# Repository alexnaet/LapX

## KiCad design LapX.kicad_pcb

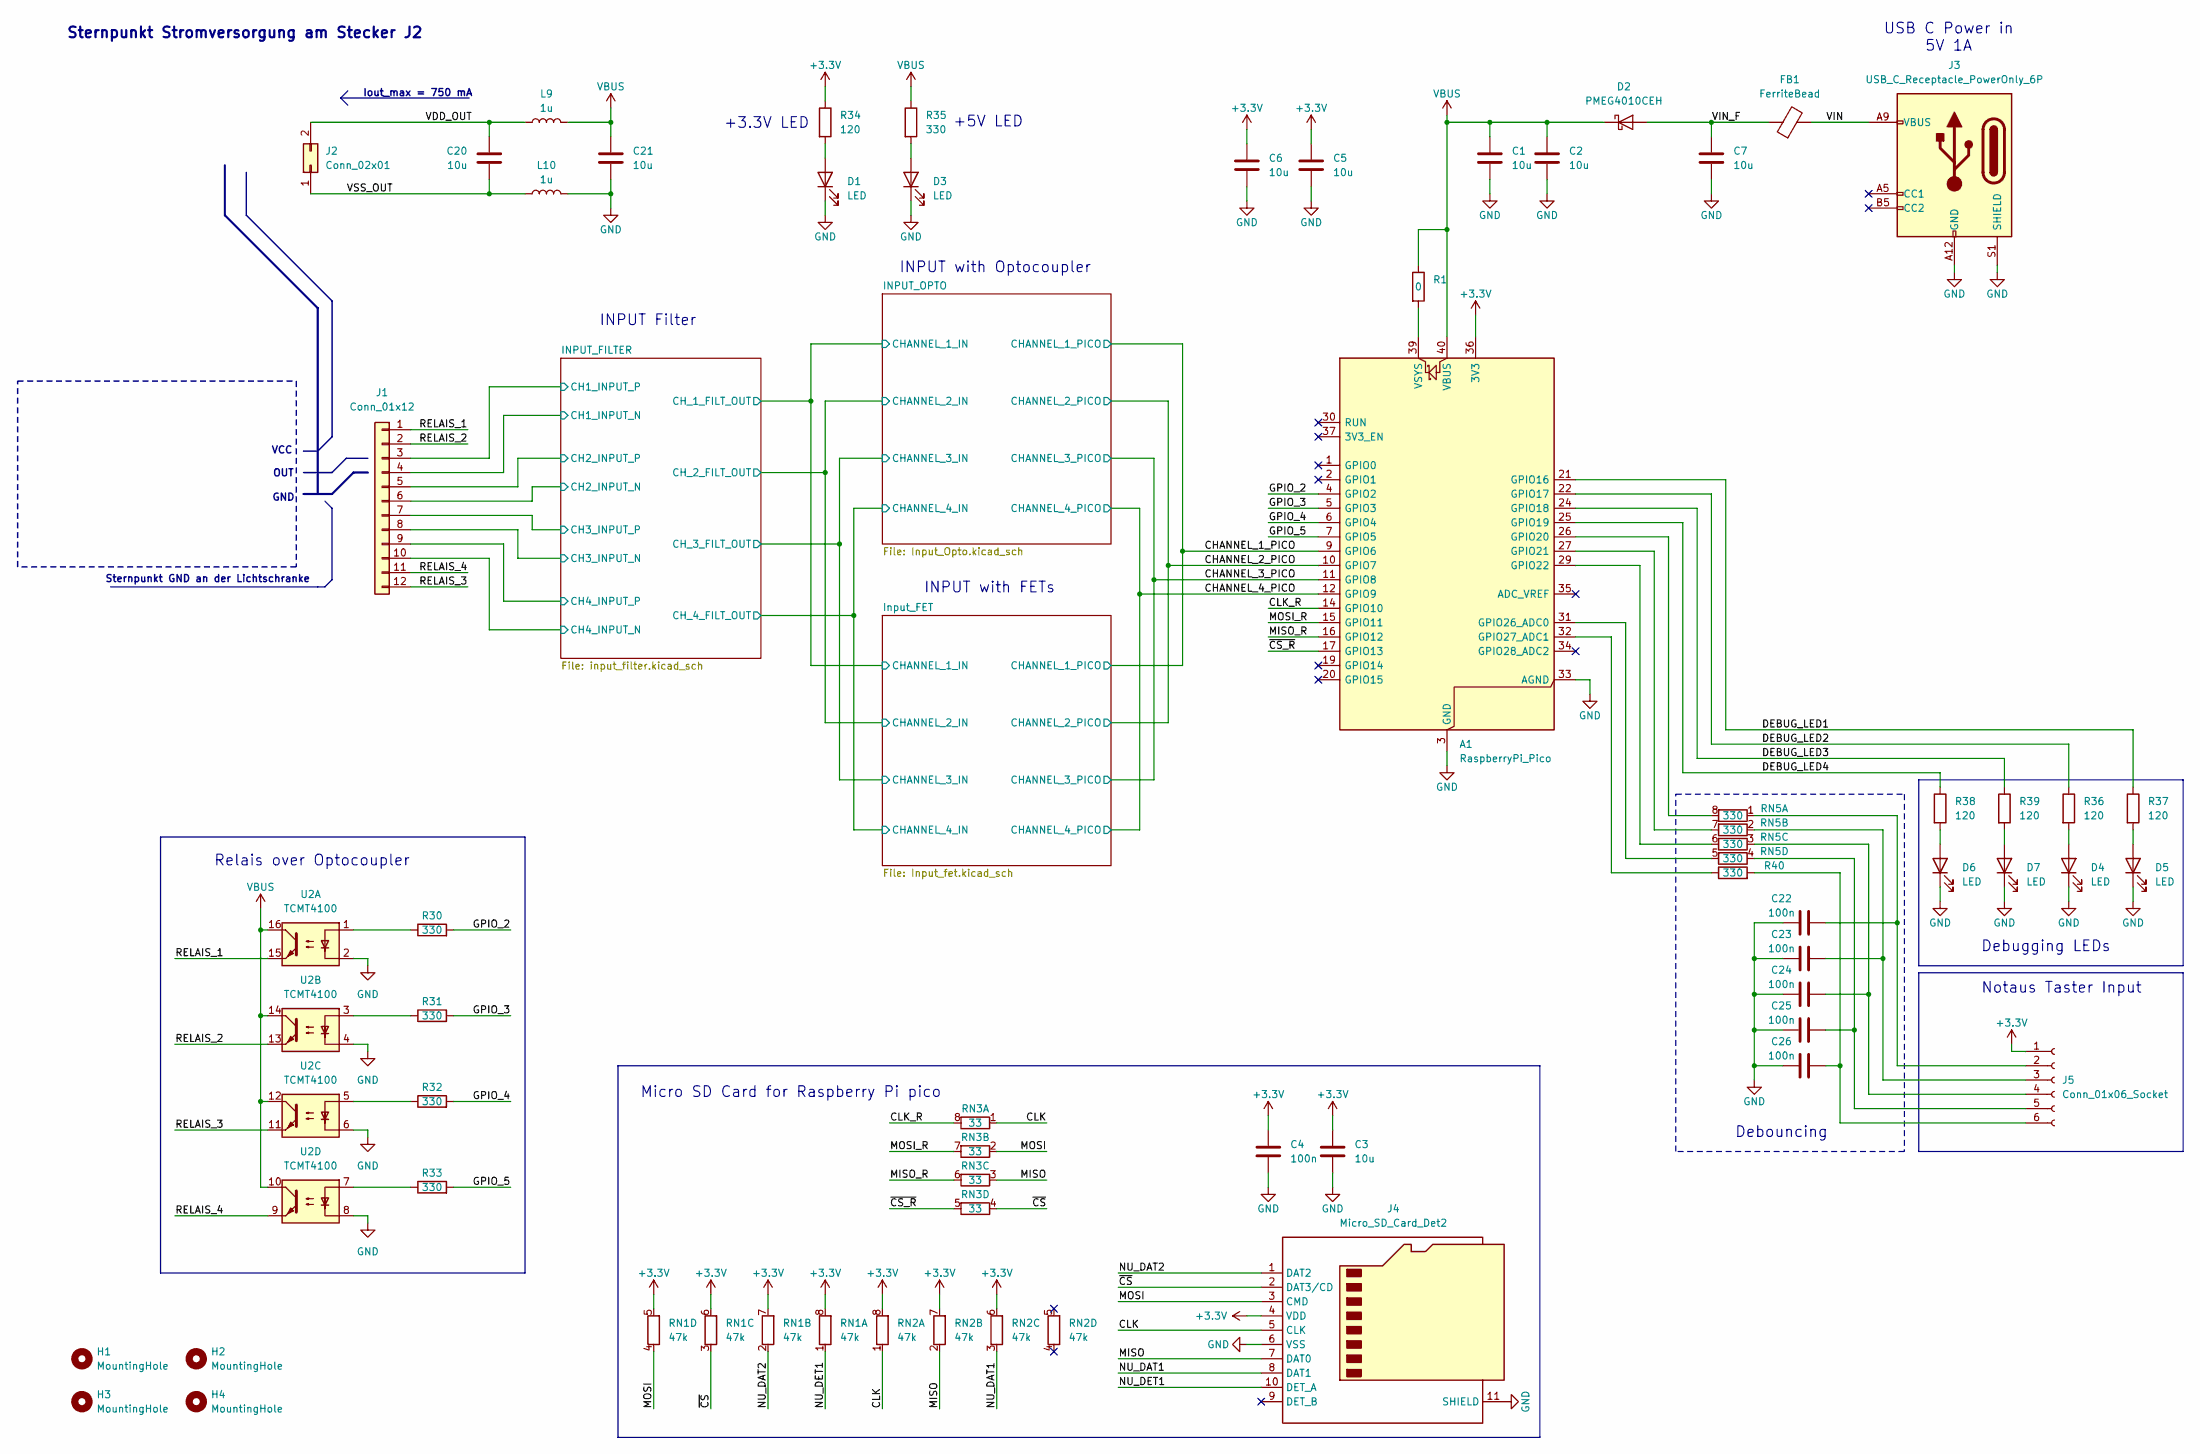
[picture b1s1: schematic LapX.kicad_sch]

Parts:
A1: RaspberryPi_Pico; RaspberryPi_Pico_Common_THT
C1, C2, C3, C5, C6, C7: 10u; C_0805_2012Metric
C4, C22, C23, C24, C25, C26: 100n; C_0603_1608Metric
C20, C21: 10u; C_0603_1608Metric
D1, D3, D4, D5, D6, D7: LED; LED_0603_1608Metric
D2: PMEG4010CEH; D_SOD-123F; LCSC C193342
FB1: FerriteBead; L_0603_1608Metric
H1, H2, H3, H4: MountingHole; MountingHole_3.2mm_M3_DIN965_Pad_TopBottom
J1: Conn_01x12; PHOENIX_1725753
J2: Conn_02x01; PHOENIX_1725656
J3: USB_C_Receptacle_PowerOnly_6P; USB_C_Receptacle_GCT_USB4125-xx-x_6P_TopMnt_Horizontal
J4: Micro_SD_Card_Det2; microSD_HC_Molex_104031-0811
J5: Conn_01x06_Socket; PinHeader_1x06_P2.54mm_Vertical
L9, L10: 1u; L_0805_2012Metric
R1: 0; R_0603_1608Metric
R30, R31, R32, R33, R35, R40: 330; R_0603_1608Metric
R34, R36, R37, R38, R39: 120; R_0603_1608Metric
RN1, RN2: 47k; R_Array_Convex_4x0603
RN3: 33; R_Array_Convex_4x0603
RN5: 330; R_Array_Convex_4x0603
U2: TCMT4100; SOP-16_4.4x10.4mm_P1.27mm

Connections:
+3.3V: A1.36 (3V3), C3.1, C4.1, C5.1, C6.1, J4.4 (VDD), J5.1, R34.1, RN1.5 (R4.2), RN1.6 (R3.2), RN1.7 (R2.2), RN1.8 (R1.2), RN2.6 (R3.2), RN2.7 (R2.2), RN2.8 (R1.2); also elsewhere on the board
/CHANNEL_1_PICO: A1.9 (GPIO6); also elsewhere on the board
/CHANNEL_2_PICO: A1.10 (GPIO7); also elsewhere on the board
/CHANNEL_3_PICO: A1.11 (GPIO8); also elsewhere on the board
/CHANNEL_4_PICO: A1.12 (GPIO9); also elsewhere on the board
/CLK: J4.5 (CLK), RN2.1 (R1.1), RN3.1 (R1.1)
/CLK_R: A1.14 (GPIO10), RN3.8 (R1.2)
/DEBUG_LED1: A1.21 (GPIO16), R37.1
/DEBUG_LED2: A1.22 (GPIO17), R36.1
/DEBUG_LED3: A1.24 (GPIO18), R39.1
/DEBUG_LED4: A1.25 (GPIO19), R38.1
/GPIO_2: A1.4 (GPIO2), R30.2
/GPIO_3: A1.5 (GPIO3), R31.2
/GPIO_4: A1.6 (GPIO4), R32.2
/GPIO_5: A1.7 (GPIO5), R33.2
/INPUT_FILTER/CH1_INPUT_N: J1.4; also elsewhere on the board
/INPUT_FILTER/CH1_INPUT_P: J1.3; also elsewhere on the board
/INPUT_FILTER/CH2_INPUT_N: J1.6; also elsewhere on the board
/INPUT_FILTER/CH2_INPUT_P: J1.5; also elsewhere on the board
/INPUT_FILTER/CH3_INPUT_N: J1.8; also elsewhere on the board
/INPUT_FILTER/CH3_INPUT_P: J1.7; also elsewhere on the board
/INPUT_FILTER/CH4_INPUT_N: J1.10; also elsewhere on the board
/INPUT_FILTER/CH4_INPUT_P: J1.9; also elsewhere on the board
/MISO: J4.7 (DAT0), RN2.2 (R2.1), RN3.3 (R3.1)
/MISO_R: A1.16 (GPIO12), RN3.6 (R3.2)
/MOSI: J4.3 (CMD), RN1.4 (R4.1), RN3.2 (R2.1)
/MOSI_R: A1.15 (GPIO11), RN3.7 (R2.2)
/NU_DAT1: J4.8 (DAT1), RN2.3 (R3.1)
/NU_DAT2: J4.1 (DAT2), RN1.2 (R2.1)
/NU_DET1: J4.10 (DET_A), RN1.1 (R1.1)
/RELAIS_1: J1.1, U2.15
/RELAIS_2: J1.2, U2.13
/RELAIS_3: J1.12, U2.11
/RELAIS_4: J1.11, U2.9
/VDD_OUT: C20.1, J2.2, L9.1
/VIN: FB1.2, J3.A9 (VBUS), J3.B9 (VBUS)
/VIN_F: C7.1, D2.2 (A), FB1.1
/VSS_OUT: C20.2, J2.1, L10.1
/~CS_R: A1.17 (GPIO13), RN3.5 (R4.2)
/~CS: J4.2 (DAT3/CD), RN1.3 (R3.1), RN3.4 (R4.1)
GND: A1.3 (GND), A1.8 (GND), A1.13 (GND), A1.18 (GND), A1.23 (GND), A1.28 (GND), A1.33 (AGND), A1.38 (GND), C1.2, C2.2, C3.2, C4.2, C5.2, C6.2, C7.2, C21.2, C22.1, C23.1, C24.1, C25.1, C26.1, D1.1 (K), D3.1 (K), D4.1 (K), D5.1 (K), D6.1 (K), D7.1 (K), J3.A12 (GND), J3.B12 (GND), J3.S1 (SHIELD), J4.6 (VSS), J4.11 (SHIELD), L10.2, U2.2, U2.4, U2.6, U2.8; also elsewhere on the board
unnamed: A1.26 (GPIO20), RN5.8 (R1.2)
unnamed: A1.27 (GPIO21), RN5.7 (R2.2)
unnamed: A1.29 (GPIO22), RN5.6 (R3.2)
unnamed: A1.31 (GPIO26_ADC0), RN5.5 (R4.2)
unnamed: A1.32 (GPIO27_ADC1), R40.1
unnamed: A1.39 (VSYS), R1.2
unnamed: D1.2 (A), R34.2
unnamed: D3.2 (A), R35.2
unnamed: D4.2 (A), R36.2
unnamed: D5.2 (A), R37.2
unnamed: D6.2 (A), R38.2
unnamed: D7.2 (A), R39.2
unnamed: C22.2, J5.2, RN5.1 (R1.1)
unnamed: C23.2, J5.3, RN5.2 (R2.1)
unnamed: C24.2, J5.4, RN5.3 (R3.1)
unnamed: C25.2, J5.5, RN5.4 (R4.1)
unnamed: C26.2, J5.6, R40.2
unnamed: R30.1, U2.1
unnamed: R31.1, U2.3
unnamed: R32.1, U2.5
unnamed: R33.1, U2.7
VBUS: A1.40 (VBUS), C1.1, C2.1, C21.1, D2.1 (K), L9.2, R1.1, R35.1, U2.10, U2.12, U2.14, U2.16

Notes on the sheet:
Sternpunkt Stromversorgung am Stecker J2
VCC
Notaus Taster Input
Relais over Optocoupler
Iout_max = 750 mA
INPUT with FETs
Debouncing
Debugging LEDs
+5V LED
GND
Sternpunkt GND an der Lichtschranke
USB C Power in 5V 1A
INPUT with Optocoupler
+3.3V LED
INPUT Filter
OUT
Micro SD Card for Raspberry Pi pico

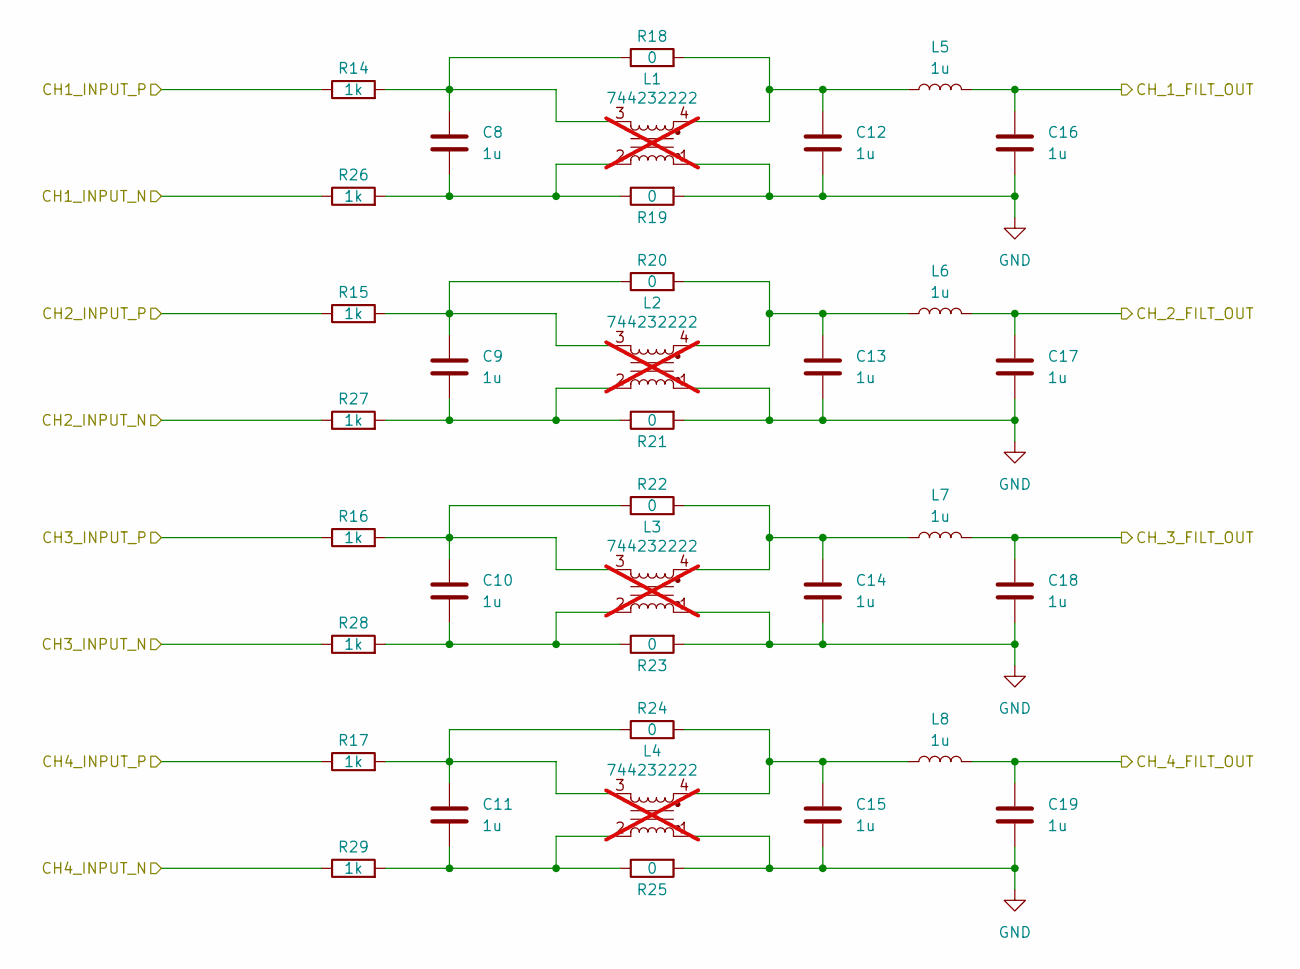
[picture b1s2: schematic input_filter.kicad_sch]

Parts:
C8, C9, C10, C11, C12, C13, C14, C15, C16, C17, C18, C19: 1u; C_0603_1608Metric
L1, L2, L3, L4: 744232222; L_CommonMode_Wurth_WE-CNSW-1206; not fitted
L5, L6, L7, L8: 1u; L_0805_2012Metric
R14, R15, R16, R17, R26, R27, R28, R29: 1k; R_0603_1608Metric
R18, R19, R20, R21, R22, R23, R24, R25: 0; R_0603_1608Metric

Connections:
/INPUT_FILTER/CH1_INPUT_N: R26.1; also elsewhere on the board
/INPUT_FILTER/CH1_INPUT_P: R14.1; also elsewhere on the board
/INPUT_FILTER/CH2_INPUT_N: R27.1; also elsewhere on the board
/INPUT_FILTER/CH2_INPUT_P: R15.1; also elsewhere on the board
/INPUT_FILTER/CH3_INPUT_N: R28.1; also elsewhere on the board
/INPUT_FILTER/CH3_INPUT_P: R16.1; also elsewhere on the board
/INPUT_FILTER/CH4_INPUT_N: R29.1; also elsewhere on the board
/INPUT_FILTER/CH4_INPUT_P: R17.1; also elsewhere on the board
/INPUT_FILTER/CH_1_FILT_OUT: C16.1, L5.2; also elsewhere on the board
/INPUT_FILTER/CH_2_FILT_OUT: C17.1, L6.2; also elsewhere on the board
/INPUT_FILTER/CH_3_FILT_OUT: C18.1, L7.2; also elsewhere on the board
/INPUT_FILTER/CH_4_FILT_OUT: C19.1, L8.2; also elsewhere on the board
GND: C12.2, C13.2, C14.2, C15.2, C16.2, C17.2, C18.2, C19.2, L1.1, L2.1, L3.1, L4.1, R19.2, R21.2, R23.2, R25.2; also elsewhere on the board
unnamed: C8.1, L1.3, R14.2, R18.1
unnamed: C8.2, L1.2, R19.1, R26.2
unnamed: C9.1, L2.3, R15.2, R20.1
unnamed: C9.2, L2.2, R21.1, R27.2
unnamed: C10.1, L3.3, R16.2, R22.1
unnamed: C10.2, L3.2, R23.1, R28.2
unnamed: C11.1, L4.3, R17.2, R24.1
unnamed: C11.2, L4.2, R25.1, R29.2
unnamed: C12.1, L1.4, L5.1, R18.2
unnamed: C13.1, L2.4, L6.1, R20.2
unnamed: C14.1, L3.4, L7.1, R22.2
unnamed: C15.1, L4.4, L8.1, R24.2

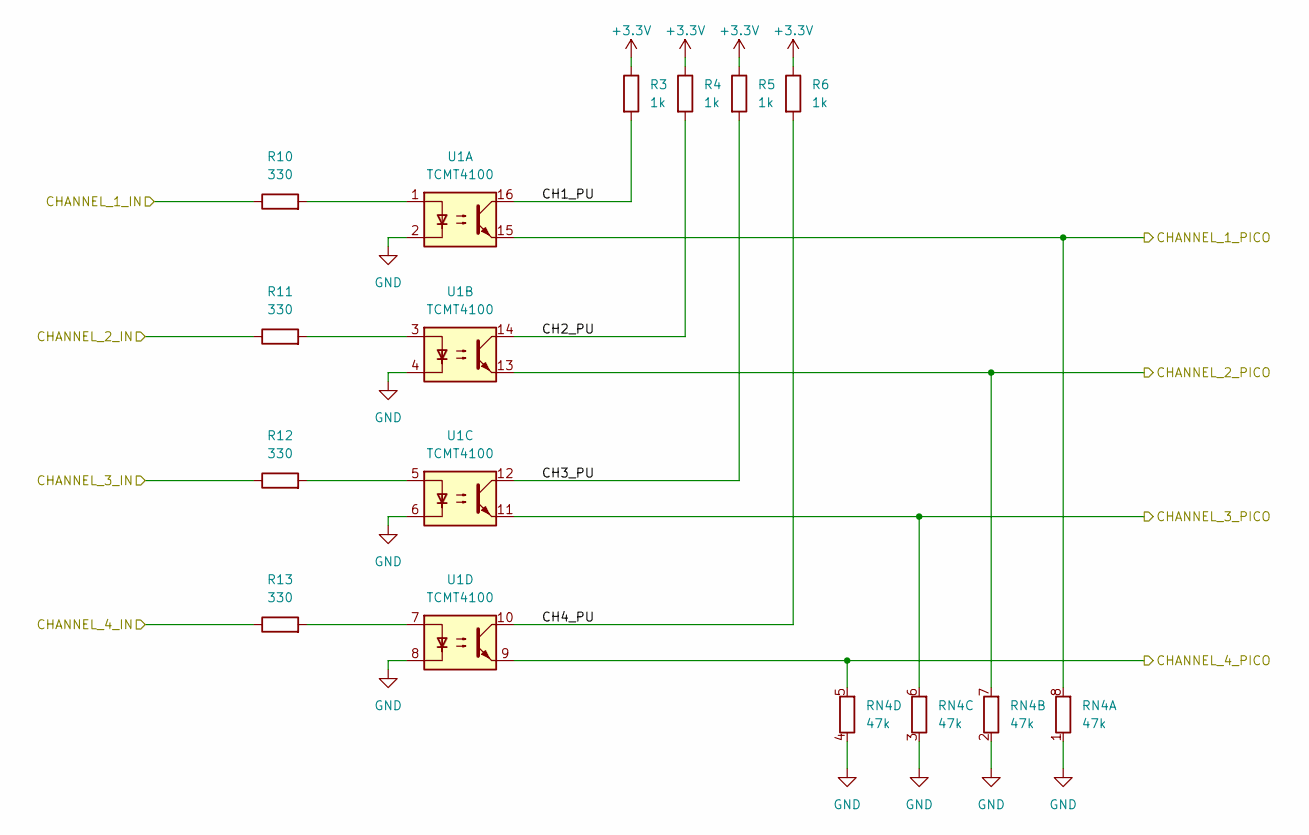
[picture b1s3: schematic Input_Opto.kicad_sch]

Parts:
R3, R4, R5, R6: 1k; R_0603_1608Metric
R10, R11, R12, R13: 330; R_0603_1608Metric
RN4: 47k; R_Array_Convex_4x0603
U1: TCMT4100; SOP-16_4.4x10.4mm_P1.27mm

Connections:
+3.3V: R3.1, R4.1, R5.1, R6.1; also elsewhere on the board
/CHANNEL_1_PICO: RN4.8 (R1.2), U1.15; also elsewhere on the board
/CHANNEL_2_PICO: RN4.7 (R2.2), U1.13; also elsewhere on the board
/CHANNEL_3_PICO: RN4.6 (R3.2), U1.11; also elsewhere on the board
/CHANNEL_4_PICO: RN4.5 (R4.2), U1.9; also elsewhere on the board
/INPUT_FILTER/CH_1_FILT_OUT: R10.1; also elsewhere on the board
/INPUT_FILTER/CH_2_FILT_OUT: R11.1; also elsewhere on the board
/INPUT_FILTER/CH_3_FILT_OUT: R12.1; also elsewhere on the board
/INPUT_FILTER/CH_4_FILT_OUT: R13.1; also elsewhere on the board
/INPUT_OPTO/CH1_PU: R3.2, U1.16
/INPUT_OPTO/CH2_PU: R4.2, U1.14
/INPUT_OPTO/CH3_PU: R5.2, U1.12
/INPUT_OPTO/CH4_PU: R6.2, U1.10
GND: RN4.1 (R1.1), RN4.2 (R2.1), RN4.3 (R3.1), RN4.4 (R4.1), U1.2, U1.4, U1.6, U1.8; also elsewhere on the board
unnamed: R10.2, U1.1
unnamed: R11.2, U1.3
unnamed: R12.2, U1.5
unnamed: R13.2, U1.7

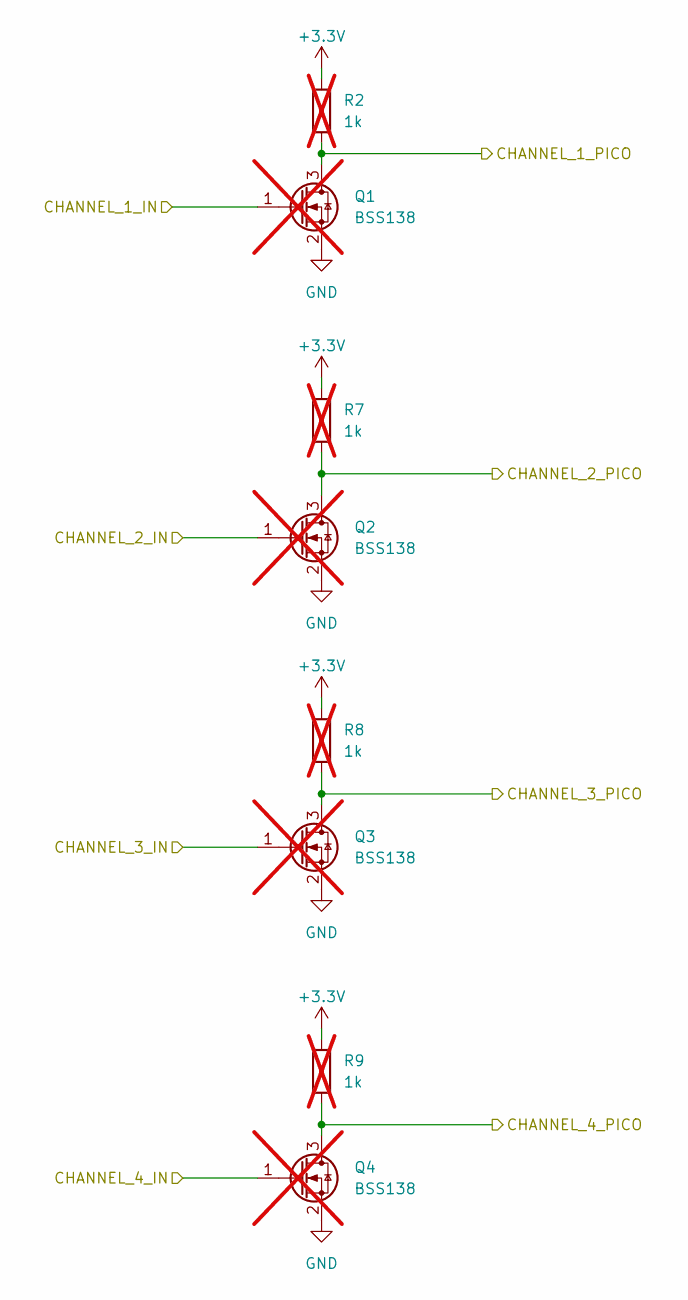
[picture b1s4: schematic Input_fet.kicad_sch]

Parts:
Q1, Q2, Q3, Q4: BSS138; SOT-23; not fitted
R2, R7, R8, R9: 1k; R_0603_1608Metric; not fitted

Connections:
+3.3V: R2.1, R7.1, R8.1, R9.1; also elsewhere on the board
/CHANNEL_1_PICO: Q1.3 (D), R2.2; also elsewhere on the board
/CHANNEL_2_PICO: Q2.3 (D), R7.2; also elsewhere on the board
/CHANNEL_3_PICO: Q3.3 (D), R8.2; also elsewhere on the board
/CHANNEL_4_PICO: Q4.3 (D), R9.2; also elsewhere on the board
/INPUT_FILTER/CH_1_FILT_OUT: Q1.1 (G); also elsewhere on the board
/INPUT_FILTER/CH_2_FILT_OUT: Q2.1 (G); also elsewhere on the board
/INPUT_FILTER/CH_3_FILT_OUT: Q3.1 (G); also elsewhere on the board
/INPUT_FILTER/CH_4_FILT_OUT: Q4.1 (G); also elsewhere on the board
GND: Q1.2 (S), Q2.2 (S), Q3.2 (S), Q4.2 (S); also elsewhere on the board

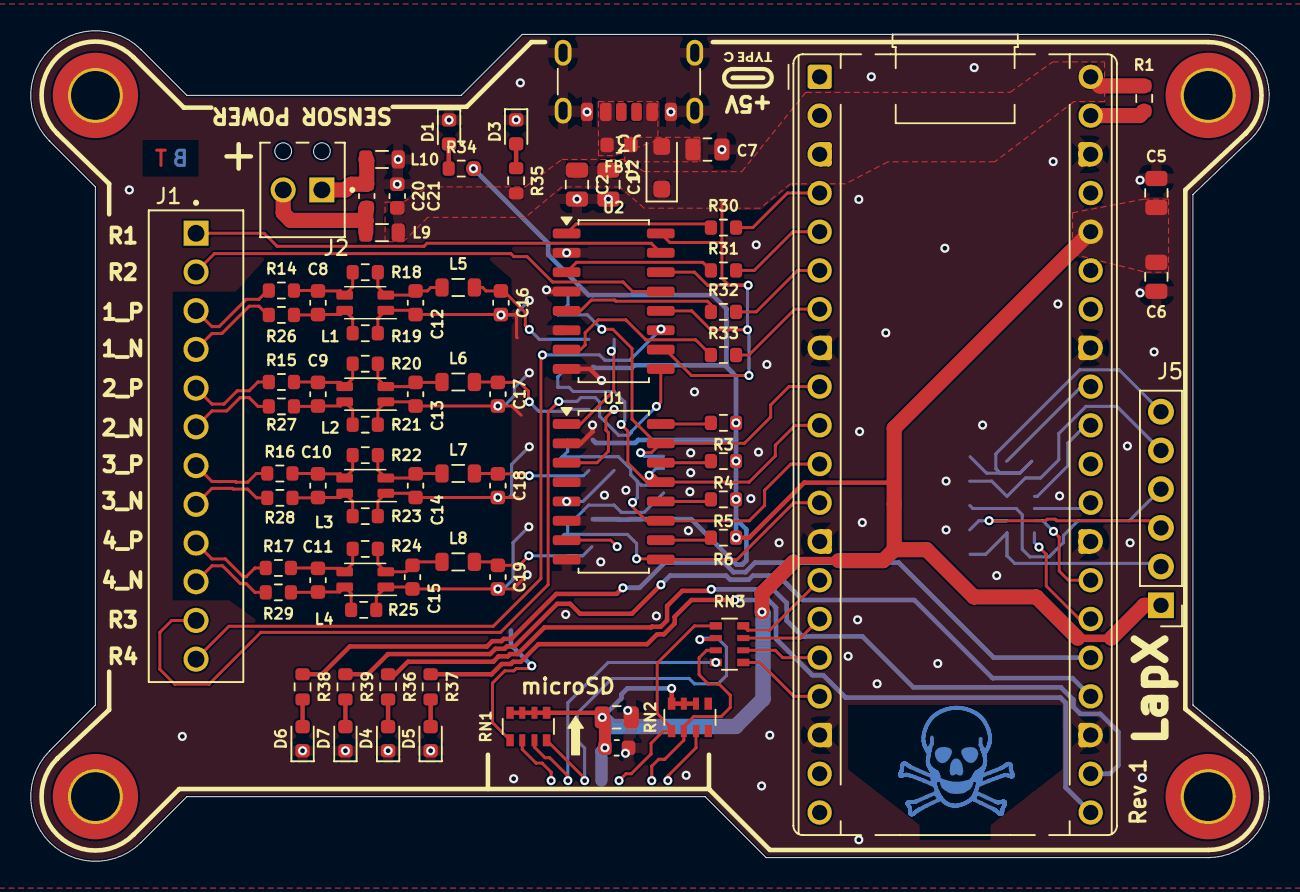
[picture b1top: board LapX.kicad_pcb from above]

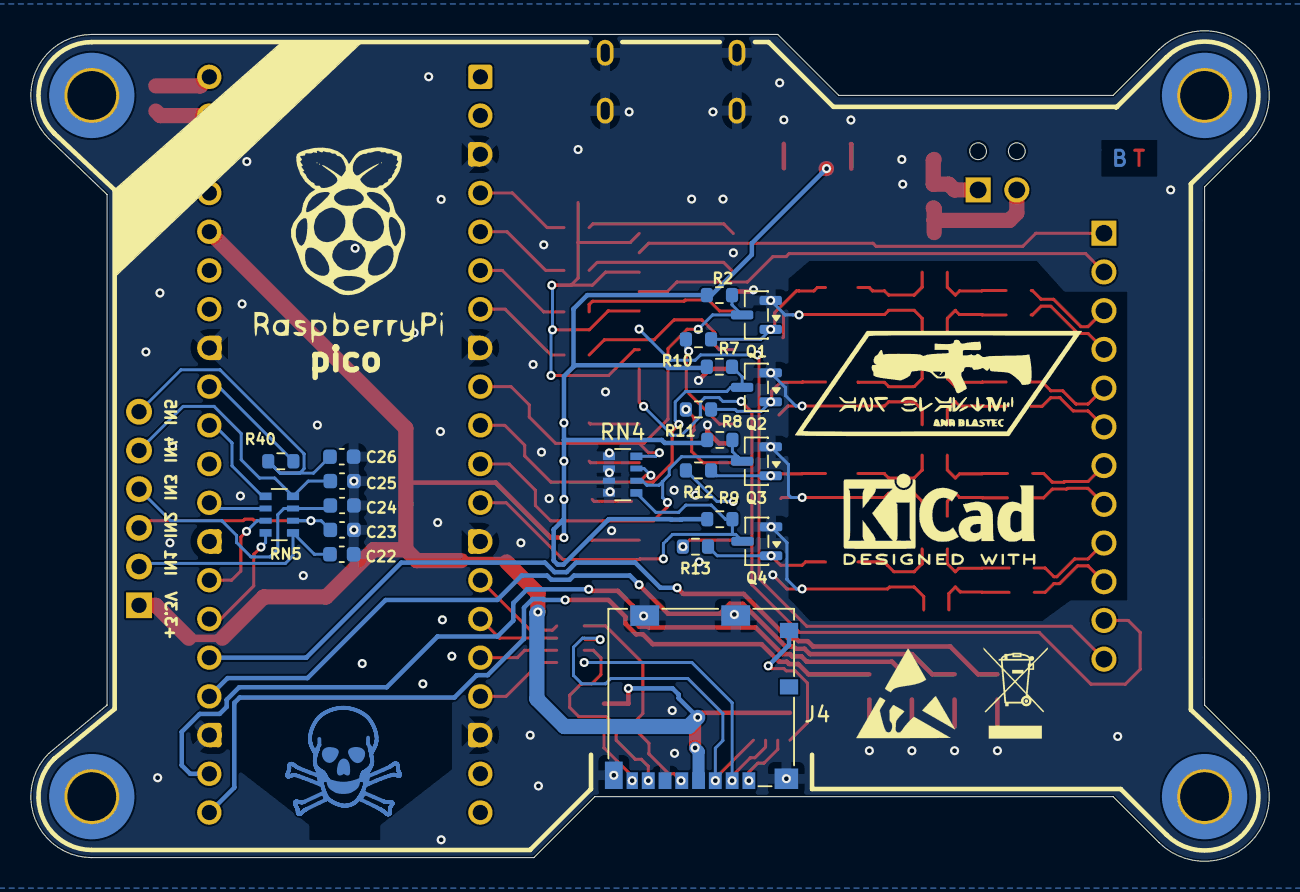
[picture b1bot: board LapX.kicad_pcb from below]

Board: 2 copper layers, 81.2 x 54.5 mm, 105 parts (21 on the bottom side), 87 nets.

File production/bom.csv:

Designator,Footprint,Quantity,Value,LCSC Part #
A1,RaspberryPi_Pico_Common_THT,1,RaspberryPi_Pico,
"C1, C2, C3, C5, C6, C7",0805,6,10u,
"C10, C11, C12, C13, C14, C15, C16, C17, C18, C19, C8, C9",0603,12,1u,
"C20, C21",0603,2,10u,
"C22, C23, C24, C25, C26, C4",0603,6,100n,
"D1, D3, D4, D5, D6, D7",0603,6,LED,
D2,D_SOD-123F,1,PMEG4010CEH,C193342
FB1,0603,1,FerriteBead,
J1,PHOENIX_1725753,1,Conn_01x12,
J2,PHOENIX_1725656,1,Conn_02x01,
J3,USB_C_Receptacle_GCT_USB4125-xx-x_6P_TopMnt_Horizontal,1,USB_C_Receptacle_PowerOnly_6P,
J4,microSD_HC_Molex_104031-0811,1,Micro_SD_Card_Det2,
J5,PinHeader_1x06_P2.54mm_Vertical,1,Conn_01x06_Socket,
"L10, L5, L6, L7, L8, L9",0805,6,1u,
"R1, R18, R19, R20, R21, R22, R23, R24, R25",0603,9,0,
"R10, R11, R12, R13, R30, R31, R32, R33, R35, R40",0603,10,330,
"R14, R15, R16, R17, R26, R27, R28, R29, R3, R4, R5, R6",0603,12,1k,
"R34, R36, R37, R38, R39",0603,5,120,
"RN1, RN2, RN4",R_Array_Convex_4x0603,3,47k,
RN3,R_Array_Convex_4x0603,1,33,
RN5,R_Array_Convex_4x0603,1,330,
"U1, U2",SOP-16_4.4x10.4mm_P1.27mm,2,TCMT4100,

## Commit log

2026-02-15 Ärbet
2026-02-15 Submit
2026-02-15 Layout nearly done
2026-02-19 Layout fast fertig
2026-02-20 Layout nearly finished
2026-02-22 Letzte Changes
2026-02-22 Order placed, Layout and Schematic finished
2026-02-24 Bestellt
2026-03-11 Nix wirklich gemacht
2026-03-17 Weiß nicht
2026-03-21 Small stuff
